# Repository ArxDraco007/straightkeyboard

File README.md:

# ArxKeyboard - A Custom Keyboard
## Building a custom mechanical keyboard from scratch.

## Why did I make this project?
Keyboards are a crucial part and parcel of your everyday life and efficiency, and it is crucial for you to have the very best.
It is also a very fun project to make, and it is also very cool to have your own custom keyboard.

## Description
This keyboard is a full-size mechanical keyboard. This has a custom PCB built around an ESP32-S3 WROOM. It contains a 6x17 switch matrix. It is a  two-piece case, red top shell over a blue base, designed in Fusion 360 and printed to match hole-for-hole with the PCB mounting points. It is running KMK on the firmware side.

## Pictures - 
The Schematic

The PCB

The CAD Model

## Zine

# Bill of Materials (BOM)

| Ref. | Value / Part Number | Footprint | Qty. | Supplier | Link | Notes |
|:---|:---|:---|---:|:---|:---|:---|
| C1 | 100 nF | 0603 | 1 | Robu.in | [100 nF 0603 — Pack of 40](https://robu.in/product/100nf-0603-surface-mount-multilayer-ceramic-capacitor-pack-of-40) | X7R, 50 V |
| C2 | 22 nF | 0603 | 1 | Robu.in | [22 nF 0603 — Pack of 50](https://robu.in/product/22nf-0603-surface-mount-multilayer-ceramic-capacitor-pack-of-50/) | 0603 MLCC |
| C11 | 10 µF | EIA-3216-18 (Case A) | 1 | Robu.in | [Vishay 10 µF 16 V Tantalum](https://robu.in/product/293d106x0016a2te3-vishay-tantalum-capacitor-10uf-16v-3-ohm-0-2-3216-18) | Vishay, 10 µF, 16 V; check stock |
| C12 | 22 µF | EIA-3216-18 (Case A) | 1 | element14 India | [22 µF 3216 Tantalum](https://in.element14.com/search?st=22uF+3216+tantalum) | Source from element14 India |
| R1 | 5.1 kΩ | 0603 | 1 | Robu.in | [YAGEO RC0603JR-075K1L](https://robu.in/product/rc0603jr-075k1l-yageo-res-thick-film-0603-5-1k-ohm-5-0-1w1-10w-%C2%B1100ppm-c-pad-smd-t-r/) | USB-C CC pull-down |
| R2 | 5.1 kΩ | 0603 | 1 | Robu.in | [YAGEO RC0603JR-075K1L](https://robu.in/product/rc0603jr-075k1l-yageo-res-thick-film-0603-5-1k-ohm-5-0-1w1-10w-%C2%B1100ppm-c-pad-smd-t-r/) | USB-C CC pull-down |
| R4 | 10 kΩ | 0603 | 1 | Robu.in | [10 kΩ 0603 SMD — Pack of 100](https://robu.in/product/10k-ohm-1-4w-0603-surface-mount-chip-resistor-pack-of-100/) | 1/4 W SMD resistor |
| D1–D88 | 1N4148W-7-F | SOD-123 | 88 | Evelta.com | [1N4148W-7-F — Diodes Inc.](https://evelta.com/1n4148w-7-f-100v-300ma-fast-switching-diode-2pin-smt-sod123/) | 100 V, 300 mA; genuine Diodes Inc. |
| U1 | ESP32-S3-WROOM-1-N16R8 | Module | 1 | Robu.in | [ESP32-S3-WROOM-1-N16R8](https://robu.in/product/espressif-esp32-s3-wroom-1-n16r8-module/) | 16 MB Flash, 8 MB PSRAM |
| U2 | AMS1117-3.3 | SOT-223 | 1 | Evelta.com | [AMS1117-3.3](https://evelta.com/ams1117-3-3-advanced-monolithic-systems-3-3v-1a-ldo-voltage-regulator/) | 3.3 V, 1 A LDO |
| J1 | GCT USB4105-GF-A-060 | 16P Top-Mount SMD | 1 | element14 India | [USB4105-GF-A-060](https://in.element14.com/gct-global-connector-technology/usb4105-gf-a-060/usb-conn-2-0-type-c-r-a-rcpt-16pos/dp/3777659) | USB-C, 16-pin, top-mount SMD |
| SW1–SW88 | Cherry MX2A | PCB Mount | 88 | Meckeys.com | [Cherry MX2A — 10 Pack](https://meckeys.com/shop/accessories/keyboard-accessories/key-switches/cherry-mx2a-switch/) | ₹350 / 10-pack; ≈ ₹3,080 total |
| PCB | ArxKey, 2-Layer, 280 × 130 mm | — | 5 | JLCPCB | [JLCPCB](https://jlcpcb.com/) | Manufacturing cost: $7 |

---

## Cost Summary

| Item | Estimated Cost |
|:---|---:|
| Components | Included above |
| Cherry MX2A switches | ≈ ₹3,080 |
| PCB manufacturing — 5 boards | $7 |
| **Estimated Total** | **≈ $57** |

## Stuff You Need to Remember When Making This!!! - 
- The Case is of 5 parts, you just have to place them right and screw them properly.
- Make sure U1 is in the keepout zone.
- Flash the ESP32 before assembly for testing.
- Don't reverse Tantalum capacitors, they pop (Electroboom reference(if you get it)).
- One SOD-123 per key in the matrix facing right.
- Mount in mounting holes!
- Look at the zine and sandwich the PCB.
- Do everything right or else you're cooked.

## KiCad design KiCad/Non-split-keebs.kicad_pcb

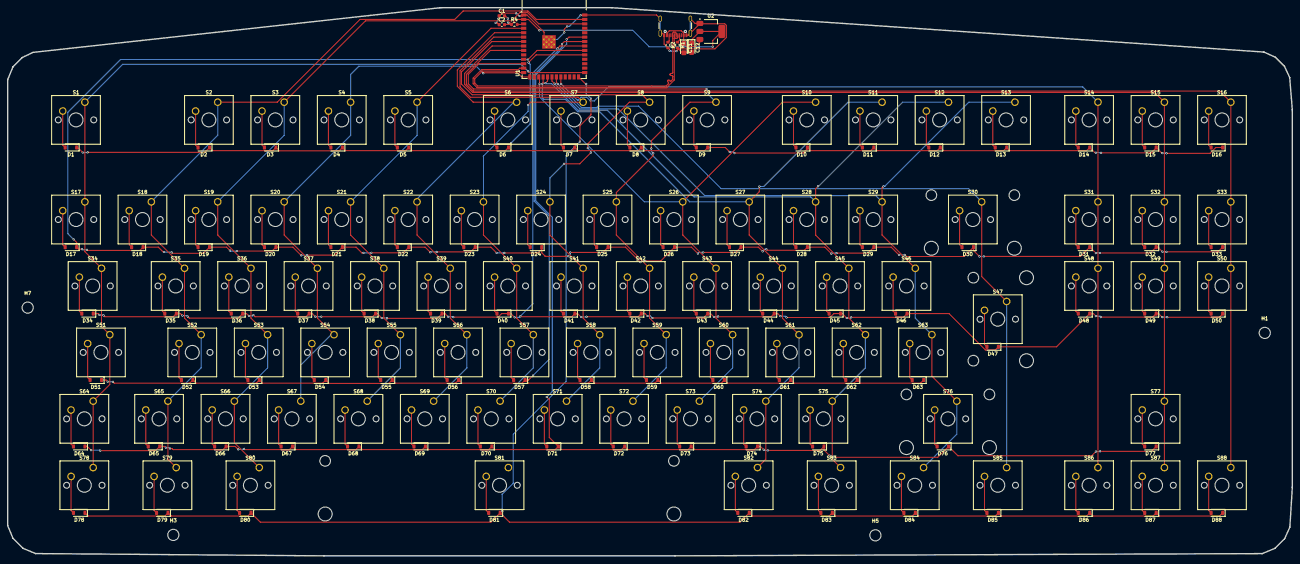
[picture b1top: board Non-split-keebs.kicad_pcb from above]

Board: 2 copper layers, 368.4 x 157.2 mm, 190 parts (0 on the bottom side), 119 nets.

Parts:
C1: 100nF; C_0603_1608Metric
C2: 22nF; C_0603_1608Metric
C11: 10uF; CP_EIA-3216-18_Kemet-A
C12: 22uF; CP_EIA-3216-18_Kemet-A
D1, D2, D3, D4, D5, D6, D7, D8, D9, D10, D11, D12, D13, D14, D15, D16, D17, D18, D19, D20, D21, D22, D23, D24, D25, D26, D27, D28, D29, D30, D31, D32, D33, D34, D35, D36, D37, D38, D39, D40, D41, D42, D43, D44, D45, D46, D47, D48, D49, D50, D51, D52, D53, D54, D55, D56, D57, D58, D59, D60, D61, D62, D63, D64, D65, D66, D67, D68, D69, D70, D71, D72, D73, D74, D75, D76, D77, D78, D79, D80, D81, D82, D83, D84, D85, D86, D87, D88: D_SOD-123
H1, H3, H5, H7: MountingHole; MountingHole_3.2mm_M3
J1: USB_C_Receptacle_USB2.0_16P; USB_C_Receptacle_GCT_USB4105-xx-A_16P_TopMnt_Horizontal
R1, R2: 5.1k; R_0603_1608Metric
R4: 10k; R_0603_1608Metric
S1, S2, S3, S4, S5, S6, S7, S8, S9, S10, S11, S12, S13, S14, S15, S16, S17, S18, S19, S20, S21, S22, S23, S24, S25, S26, S27, S28, S29, S31, S32, S33, S35, S36, S37, S38, S39, S40, S41, S42, S43, S44, S45, S46, S48, S49, S50, S52, S53, S54, S55, S56, S57, S58, S59, S60, S61, S62, S63, S65, S66, S67, S68, S69, S70, S71, S72, S73, S74, S75, S77, S79, S80, S82, S83, S84, S86, S87, S88: SW_Cherry_MX_1.00u_PCB
S30: SW_Cherry_MX_2.00u_PCB
S34: SW_Cherry_MX_1.50u_PCB
S47: SW_Cherry_MX_ISOEnter_PCB
S51: SW_Cherry_MX_1.75u_PCB
S64, S78, S85: SW_Cherry_MX_1.25u_PCB
S76: SW_Cherry_MX_2.75u_PCB
S81: SW_Cherry_MX_6.25u_PCB
U1: ESP32-S3-WROOM-1
U2: AMS1117-3.3; SOT-223-3_TabPin2

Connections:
+3V3: C1.2, C2.2, C12.1, R4.1, U1.2 (3V3), U2.2 (VO)
+5V: C11.1, J1.A4 (VBUS), J1.A9 (VBUS), J1.B4 (VBUS), J1.B9 (VBUS), U2.3 (VI)
COL0: S1.1, S17.1, S34.1, S51.1, S64.1, S78.1, U1.27 (IO0)
COL1: S2.1, S18.1, S35.1, S52.1, S65.1, S79.1, U1.39 (IO1)
COL2: S3.1, S19.1, S36.1, S53.1, S66.1, S80.1, U1.38 (IO2)
COL3: S4.1, S20.1, S37.1, S54.1, S67.1, U1.15 (IO3)
COL4: S5.1, S21.1, S38.1, S55.1, S68.1, U1.4 (IO4)
COL5: S6.1, S22.1, S39.1, S56.1, S69.1, U1.5 (IO5)
COL6: S7.1, S23.1, S40.1, S57.1, S70.1, U1.6 (IO6)
COL7: S8.1, S24.1, S41.1, S58.1, S71.1, U1.7 (IO7)
COL8: S9.1, S25.1, S42.1, S59.1, S72.1, U1.12 (IO8)
COL9: S10.1, S26.1, S43.1, S60.1, S73.1, U1.17 (IO9)
COL10: S11.1, S27.1, S44.1, S61.1, S74.1, S82.1, U1.18 (IO10)
COL11: S12.1, S28.1, S45.1, S62.1, S75.1, S83.1, U1.19 (IO11)
COL12: S13.1, S29.1, S46.1, S63.1, S76.1, S84.1, U1.20 (IO12)
COL13: S30.1, S47.1, S85.1, U1.21 (IO13)
COL14: S14.1, S31.1, S48.1, S86.1, U1.22 (IO14)
COL15: S15.1, S32.1, S49.1, S77.1, S87.1, U1.8 (IO15)
COL16: S16.1, S33.1, S50.1, S88.1, U1.9 (IO16)
D+: J1.A6 (D+), J1.B6 (D+), U1.14 (USB_D+)
D-: J1.A7 (D-), J1.B7 (D-), U1.13 (USB_D-)
GND: C1.1, C2.1, C11.2, C12.2, J1.A1 (GND), J1.A12 (GND), J1.B1 (GND), J1.B12 (GND), J1.SH (SHIELD), R1.2, R2.2, U1.1 (GND), U1.40 (GND), U1.41 (GND), U2.1 (GND)
unnamed: D1.2 (A), S1.2
unnamed: D2.2 (A), S2.2
unnamed: D3.2 (A), S3.2
unnamed: D4.2 (A), S4.2
unnamed: D5.2 (A), S5.2
unnamed: D6.2 (A), S6.2
unnamed: D7.2 (A), S7.2
unnamed: D8.2 (A), S8.2
unnamed: D9.2 (A), S9.2
unnamed: D10.2 (A), S10.2
unnamed: D11.2 (A), S11.2
unnamed: D12.2 (A), S12.2
unnamed: D13.2 (A), S13.2
unnamed: D14.2 (A), S14.2
unnamed: D15.2 (A), S15.2
unnamed: D16.2 (A), S16.2
unnamed: D17.2 (A), S17.2
unnamed: D18.2 (A), S18.2
unnamed: D19.2 (A), S19.2
unnamed: D20.2 (A), S20.2
unnamed: D21.2 (A), S21.2
unnamed: D22.2 (A), S22.2
unnamed: D23.2 (A), S23.2
unnamed: D24.2 (A), S24.2
unnamed: D25.2 (A), S25.2
unnamed: D26.2 (A), S26.2
unnamed: D27.2 (A), S27.2
unnamed: D28.2 (A), S28.2
unnamed: D29.2 (A), S29.2
unnamed: D30.2 (A), S30.2
unnamed: D31.2 (A), S31.2
unnamed: D32.2 (A), S32.2
unnamed: D33.2 (A), S33.2
unnamed: D34.2 (A), S34.2
unnamed: D35.2 (A), S35.2
unnamed: D36.2 (A), S36.2
unnamed: D37.2 (A), S37.2
unnamed: D38.2 (A), S38.2
unnamed: D39.2 (A), S39.2
unnamed: D40.2 (A), S40.2
unnamed: D41.2 (A), S41.2
unnamed: D42.2 (A), S42.2
unnamed: D43.2 (A), S43.2
unnamed: D44.2 (A), S44.2
unnamed: D45.2 (A), S45.2
unnamed: D46.2 (A), S46.2
unnamed: D47.2 (A), S47.2
unnamed: D48.2 (A), S48.2
unnamed: D49.2 (A), S49.2
unnamed: D50.2 (A), S50.2
unnamed: D51.2 (A), S51.2
unnamed: D52.2 (A), S52.2
unnamed: D53.2 (A), S53.2
unnamed: D54.2 (A), S54.2
unnamed: D55.2 (A), S55.2
unnamed: D56.2 (A), S56.2
unnamed: D57.2 (A), S57.2
unnamed: D58.2 (A), S58.2
unnamed: D59.2 (A), S59.2
unnamed: D60.2 (A), S60.2
unnamed: D61.2 (A), S61.2
unnamed: D62.2 (A), S62.2
unnamed: D63.2 (A), S63.2
unnamed: D64.2 (A), S64.2
unnamed: D65.2 (A), S65.2
unnamed: D66.2 (A), S66.2
unnamed: D67.2 (A), S67.2
unnamed: D68.2 (A), S68.2
unnamed: D69.2 (A), S69.2
unnamed: D70.2 (A), S70.2
unnamed: D71.2 (A), S71.2
unnamed: D72.2 (A), S72.2
unnamed: D73.2 (A), S73.2
unnamed: D74.2 (A), S74.2
unnamed: D75.2 (A), S75.2
unnamed: D76.2 (A), S76.2
unnamed: D77.2 (A), S77.2
unnamed: D78.2 (A), S78.2
unnamed: D79.2 (A), S79.2
unnamed: D80.2 (A), S80.2
unnamed: D81.2 (A), S81.2 (2_2)
unnamed: D82.2 (A), S82.2
unnamed: D83.2 (A), S83.2
unnamed: D84.2 (A), S84.2
unnamed: D85.2 (A), S85.2
unnamed: D86.2 (A), S86.2
unnamed: D87.2 (A), S87.2
unnamed: D88.2 (A), S88.2
unnamed: J1.A5 (CC1), R1.1
unnamed: J1.B5 (CC2), R2.1
unnamed: R4.2, U1.3 (EN)
ROW0: D1.1 (K), D2.1 (K), D3.1 (K), D4.1 (K), D5.1 (K), D6.1 (K), D7.1 (K), D8.1 (K), D9.1 (K), D10.1 (K), D11.1 (K), D12.1 (K), D13.1 (K), D14.1 (K), D15.1 (K), D16.1 (K), U1.31 (IO38)
ROW1: D17.1 (K), D18.1 (K), D19.1 (K), D20.1 (K), D21.1 (K), D22.1 (K), D23.1 (K), D24.1 (K), D25.1 (K), D26.1 (K), D27.1 (K), D28.1 (K), D29.1 (K), D30.1 (K), D31.1 (K), D32.1 (K), D33.1 (K), U1.32 (IO39)
ROW2: D34.1 (K), D35.1 (K), D36.1 (K), D37.1 (K), D38.1 (K), D39.1 (K), D40.1 (K), D41.1 (K), D42.1 (K), D43.1 (K), D44.1 (K), D45.1 (K), D46.1 (K), D47.1 (K), D48.1 (K), D49.1 (K), D50.1 (K), U1.33 (IO40)
ROW3: D51.1 (K), D52.1 (K), D53.1 (K), D54.1 (K), D55.1 (K), D56.1 (K), D57.1 (K), D58.1 (K), D59.1 (K), D60.1 (K), D61.1 (K), D62.1 (K), D63.1 (K), U1.34 (IO41)
ROW4: D64.1 (K), D65.1 (K), D66.1 (K), D67.1 (K), D68.1 (K), D69.1 (K), D70.1 (K), D71.1 (K), D72.1 (K), D73.1 (K), D74.1 (K), D75.1 (K), D76.1 (K), D77.1 (K), U1.35 (IO42)
ROW5: D78.1 (K), D79.1 (K), D80.1 (K), D81.1 (K), D82.1 (K), D83.1 (K), D84.1 (K), D85.1 (K), D86.1 (K), D87.1 (K), D88.1 (K), U1.26 (IO45)

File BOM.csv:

Ref,Value,Footprint,Qty,Supplier,Link,Notes
C1,100nF,0603,1,Robu.in,https://robu.in/product/100nf-0603-surface-mount-multilayer-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,X7R 50V
C2,22nF,0603,1,Robu.in,https://robu.in/product/22nf-0603-surface-mount-multilayer-c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,0603 MLCC
C11,10uF,EIA-3216-18 (Case A),1,Robu.in,https://robu.in/product/293d106x0016a2te3-vishay-tantalum-ca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,Vishay 10uF 16V Tantalum; check stock
C12,22uF,EIA-3216-18 (Case A),1,element14 India,https://in.element14.com/search?st=22uF+3216+tantalum,No confirmed listing on Robu/Evelta; source from element14 India
R1,5.1kΩ,0603,1,Robu.in,https://robu.in/product/rc0603jr-075k1l-yageo-res-thick-film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,USB-C CC pull-down; YAGEO RC0603JR-075K1L
R2,5.1kΩ,0603,1,Robu.in,https://robu.in/product/rc0603jr-075k1l-yageo-res-thick-film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,USB-C CC pull-down; YAGEO RC0603JR-075K1L
R4,10kΩ,0603,1,Robu.in,https://robu.in/product/10k-ohm-1-4w-0603-surface-mount-chip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,10k 1/4W 0603 SMD
D1-D88,1N4148W-7-F,SOD-123,88,Evelta.com,https://evelta.com/1n4148w-7-f-100v-300ma-fast-switching-dio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,Diodes Inc; 100V 300mA; genuine
U1,ESP32-S3-WROOM-1-N16R8,Module,1,Robu.in,https://robu.in/product/espressif-esp32-s3-wroom-1-n16r8-module/,16MB Flash 8MB PSRAM
U2,AMS1117-3.3,SOT-223,1,Evelta.com,https://evelta.com/ams1117-3-3-advanced-monolithic-systems-3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,AMS original; 1A LDO; ~₹12
J1,GCT USB4105-GF-A,16P Top Mount SMD,1,element14 India,https://in.element14.com/gct-global-connector-technology/usb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,USB-C 16P top mount SMD
SW1-SW88,Cherry MX2A,PCB Mount,88,Meckeys.com,https://meckeys.com/shop/accessories/keyboard-accessories/ke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,₹350/10 pack → ~₹3080 total

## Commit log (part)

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2026-06-14 prod files
2026-06-14 pcb and prod
2026-06-14 step and firmware
2026-06-14 BOM and Assembly files
2026-06-16 prod and pcb files
2026-06-16 updated cad files
2026-06-19 pcb files changes
2026-06-26 code.py
2026-06-26 zine
2026-06-26 Add image to Zine section in README
    Added a new image to the Zine section of the README.
